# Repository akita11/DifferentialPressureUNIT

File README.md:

# DiffPressute Unit

空気の動きも検出できるSensirion社の高感度差圧センサ[SDP810-125Pa](https://www.sensirion.com/jp/products/product-catalog/SDP810-125Pa/)で2つの口の差圧を計測し、Groveポートから計測値を送出します。計測値は搭載するATOM S3上のディスプレイで確認できます。計測されたデータは、Core2等で利用できます。（[使用例](https://twitter.com/akita11/status/1758277269104336898)）

## 設定・操作

ATOM S3のボタン（ディスプレイ面）で以下のように設定を変更できます

- シングルクリック: 画面に表示されるグラフの感度（測定値の10倍（初期値：白）→100倍（緑）→1000倍（水色）→戻る）
- ダブルクリック: データ送出周波数（20ms(50Hz)→100ms(10Hz)→5ms(200Hz)→戻る）※グラフの動く速さが変わります

## UIFlowでの使い方

UIFlow用のカスタムブロックを用意してあります（現時点ではCore2専用ですがピン割当を変更することで他のCore Basic等でも利用可能）。

- Core2のPortAに、本UnitのGroveポート(ATOM S3上)からのGroveケーブルを接続します
- UIFlowの"Custom"の"Open *.m5b"から、UIFlow/DiffPressureUNIT.m5b を開く→Custom内に"DiffPressureUnit"が追加される
- UIFlow/DiffPressureUNIT_sample.m5f"を参考に利用できます
- getDiffPressureブロックで得られる値の単位は"Pa"です。

## UART通信プロトコル

- UARTプロトコル: 115200bps, N81
- データ形式: 計測値（-32768〜+32767:符号付き16bit）の文字列＋LF('\n')

この「計測値」は、SDP810-125Paから出力される計測値です。実際の圧力への換算式はデータシートにあり、「計測値 ÷ 240 [Pa]」となります（例：計測値で"240"が1Pa）。なおSDP810-125Paのデータシートによれば、ゼロ点精度は0.08Pa、ゼロ点再現性は0.04Paです。（前述のUIFlow用カスタムブロックでは、この換算式を用いて単位[Pa]で計測値が得られます）

## Author

Junichi Akita (akita@ifdl.jp, @akita11)

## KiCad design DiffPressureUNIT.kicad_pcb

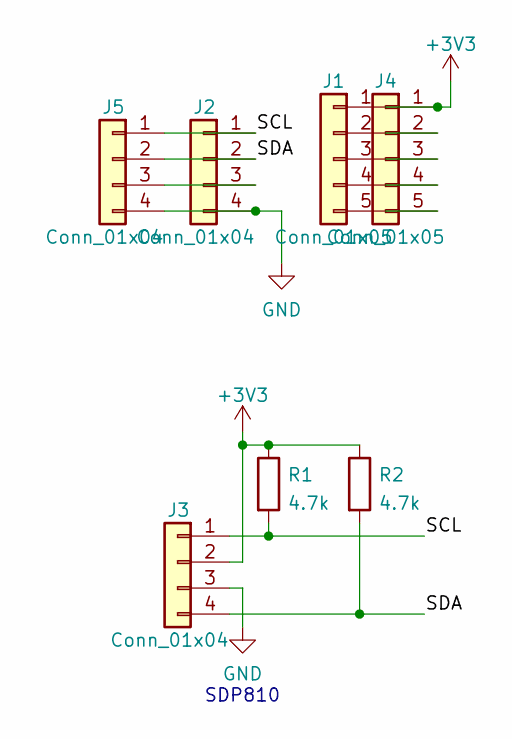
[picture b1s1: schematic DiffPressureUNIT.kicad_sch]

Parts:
J1, J4: Conn_01x05; PinHeader_1x05_P2.54mm_Vertical
J2, J5: Conn_01x04; PinHeader_1x04_P2.54mm_Vertical
J3: Conn_01x04; PinSocket_1x04_P2.00mm_Vertical
R1, R2: 4.7k; R_0603_1608Metric

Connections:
+3V3: J1.1, J3.2, J4.1, R1.1, R2.1
/SCL: J2.1, J3.1, J5.1, R1.2
/SDA: J2.2, J3.4, J5.2, R2.2
GND: J2.4, J3.3, J5.4
unnamed: J1.2, J4.2
unnamed: J1.3, J4.3
unnamed: J1.4, J4.4
unnamed: J1.5, J4.5
unnamed: J2.3, J5.3

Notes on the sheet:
SDP810

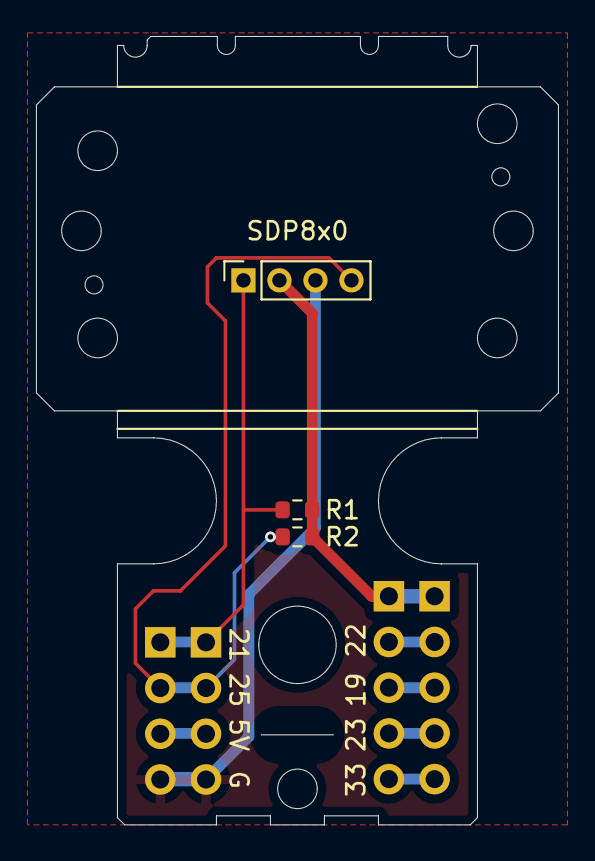
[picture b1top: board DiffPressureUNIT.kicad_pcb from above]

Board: 2 copper layers, 29.0 x 43.8 mm, 7 parts (0 on the bottom side), 9 nets.

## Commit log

2024-03-05 getDiffPressure in Pa
2024-03-05 bug fix *.m5b
